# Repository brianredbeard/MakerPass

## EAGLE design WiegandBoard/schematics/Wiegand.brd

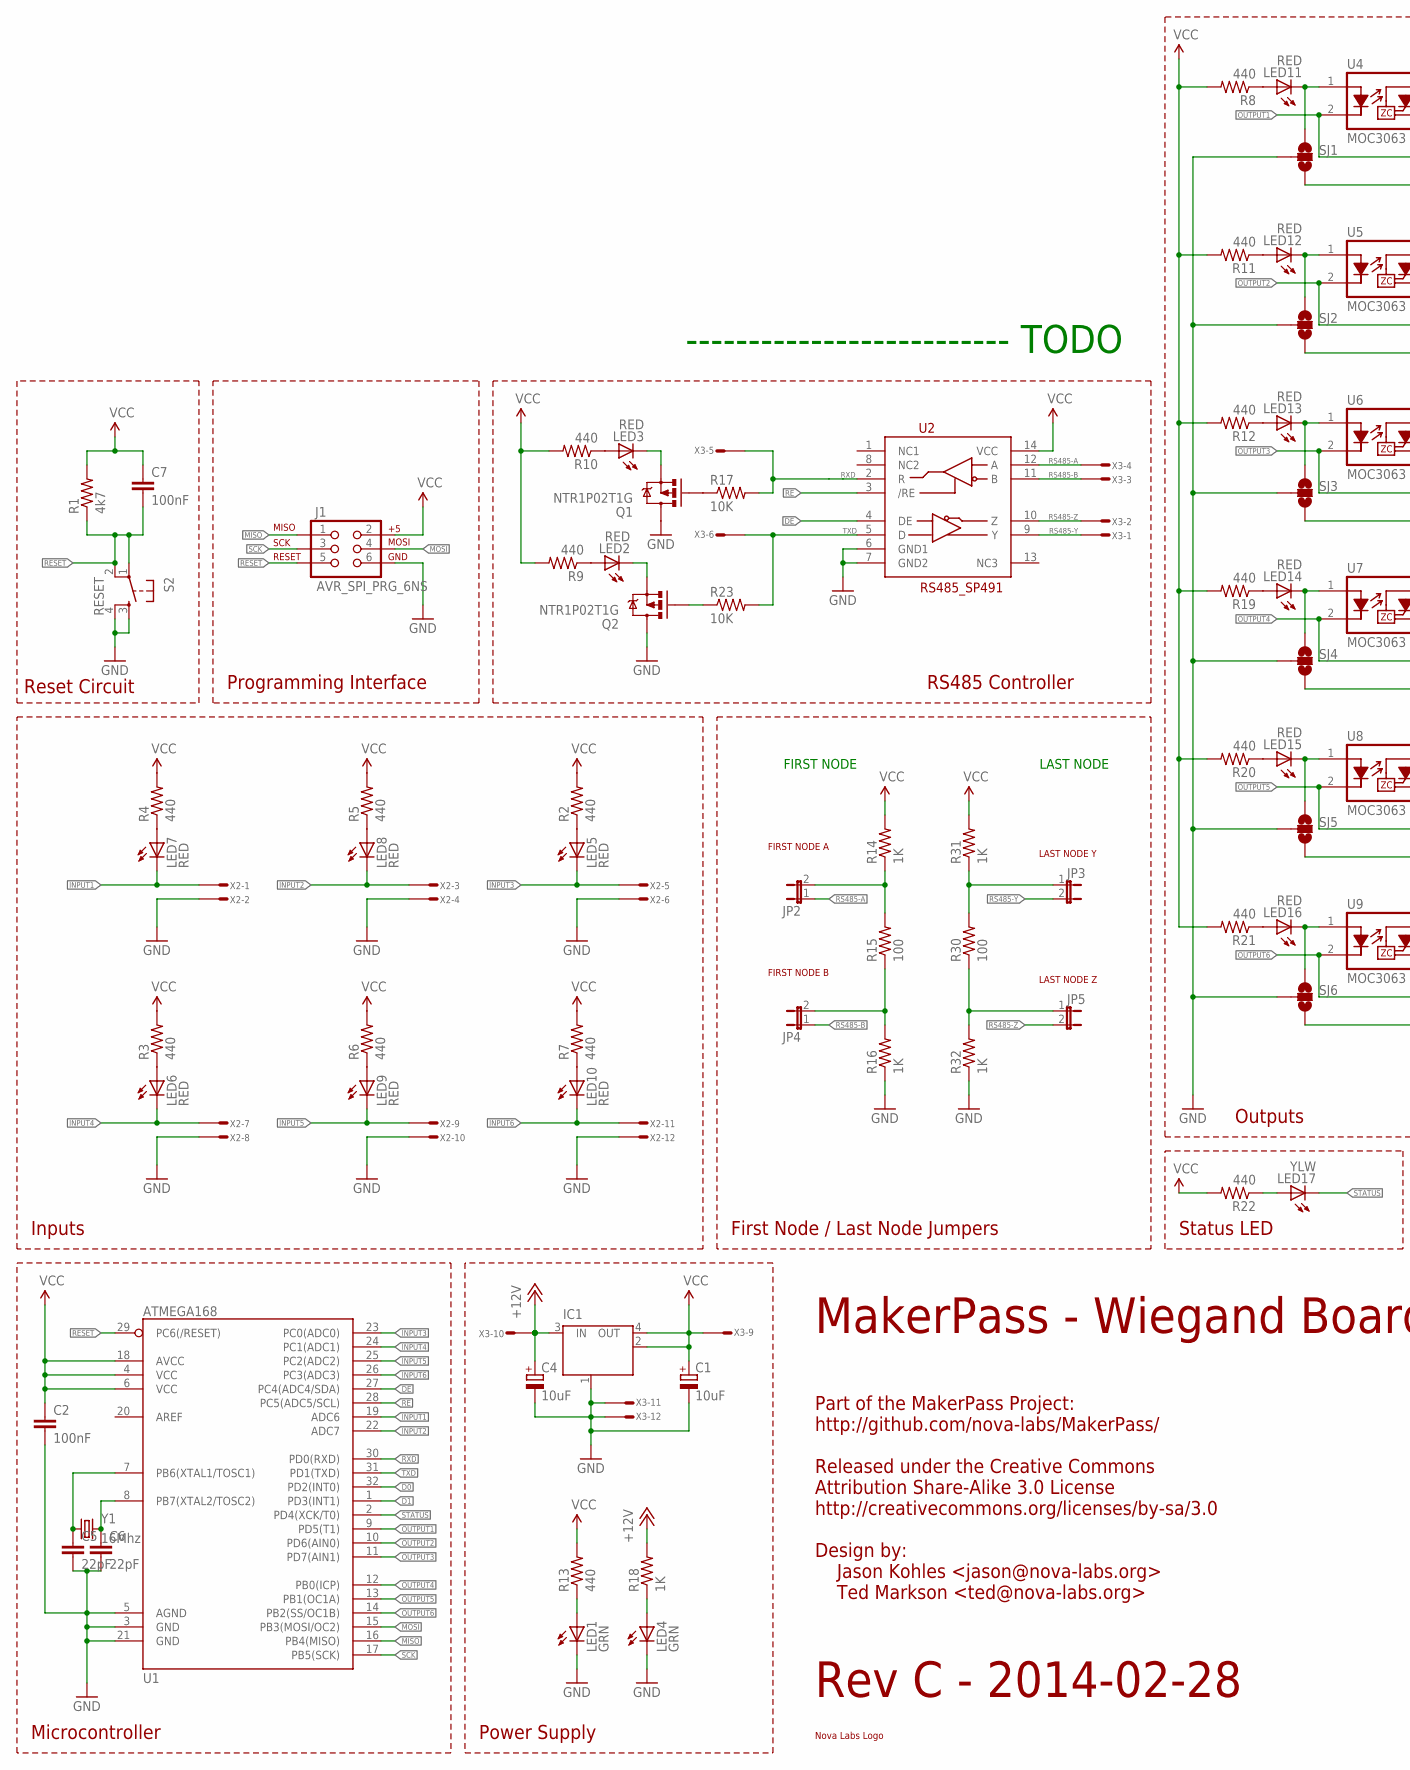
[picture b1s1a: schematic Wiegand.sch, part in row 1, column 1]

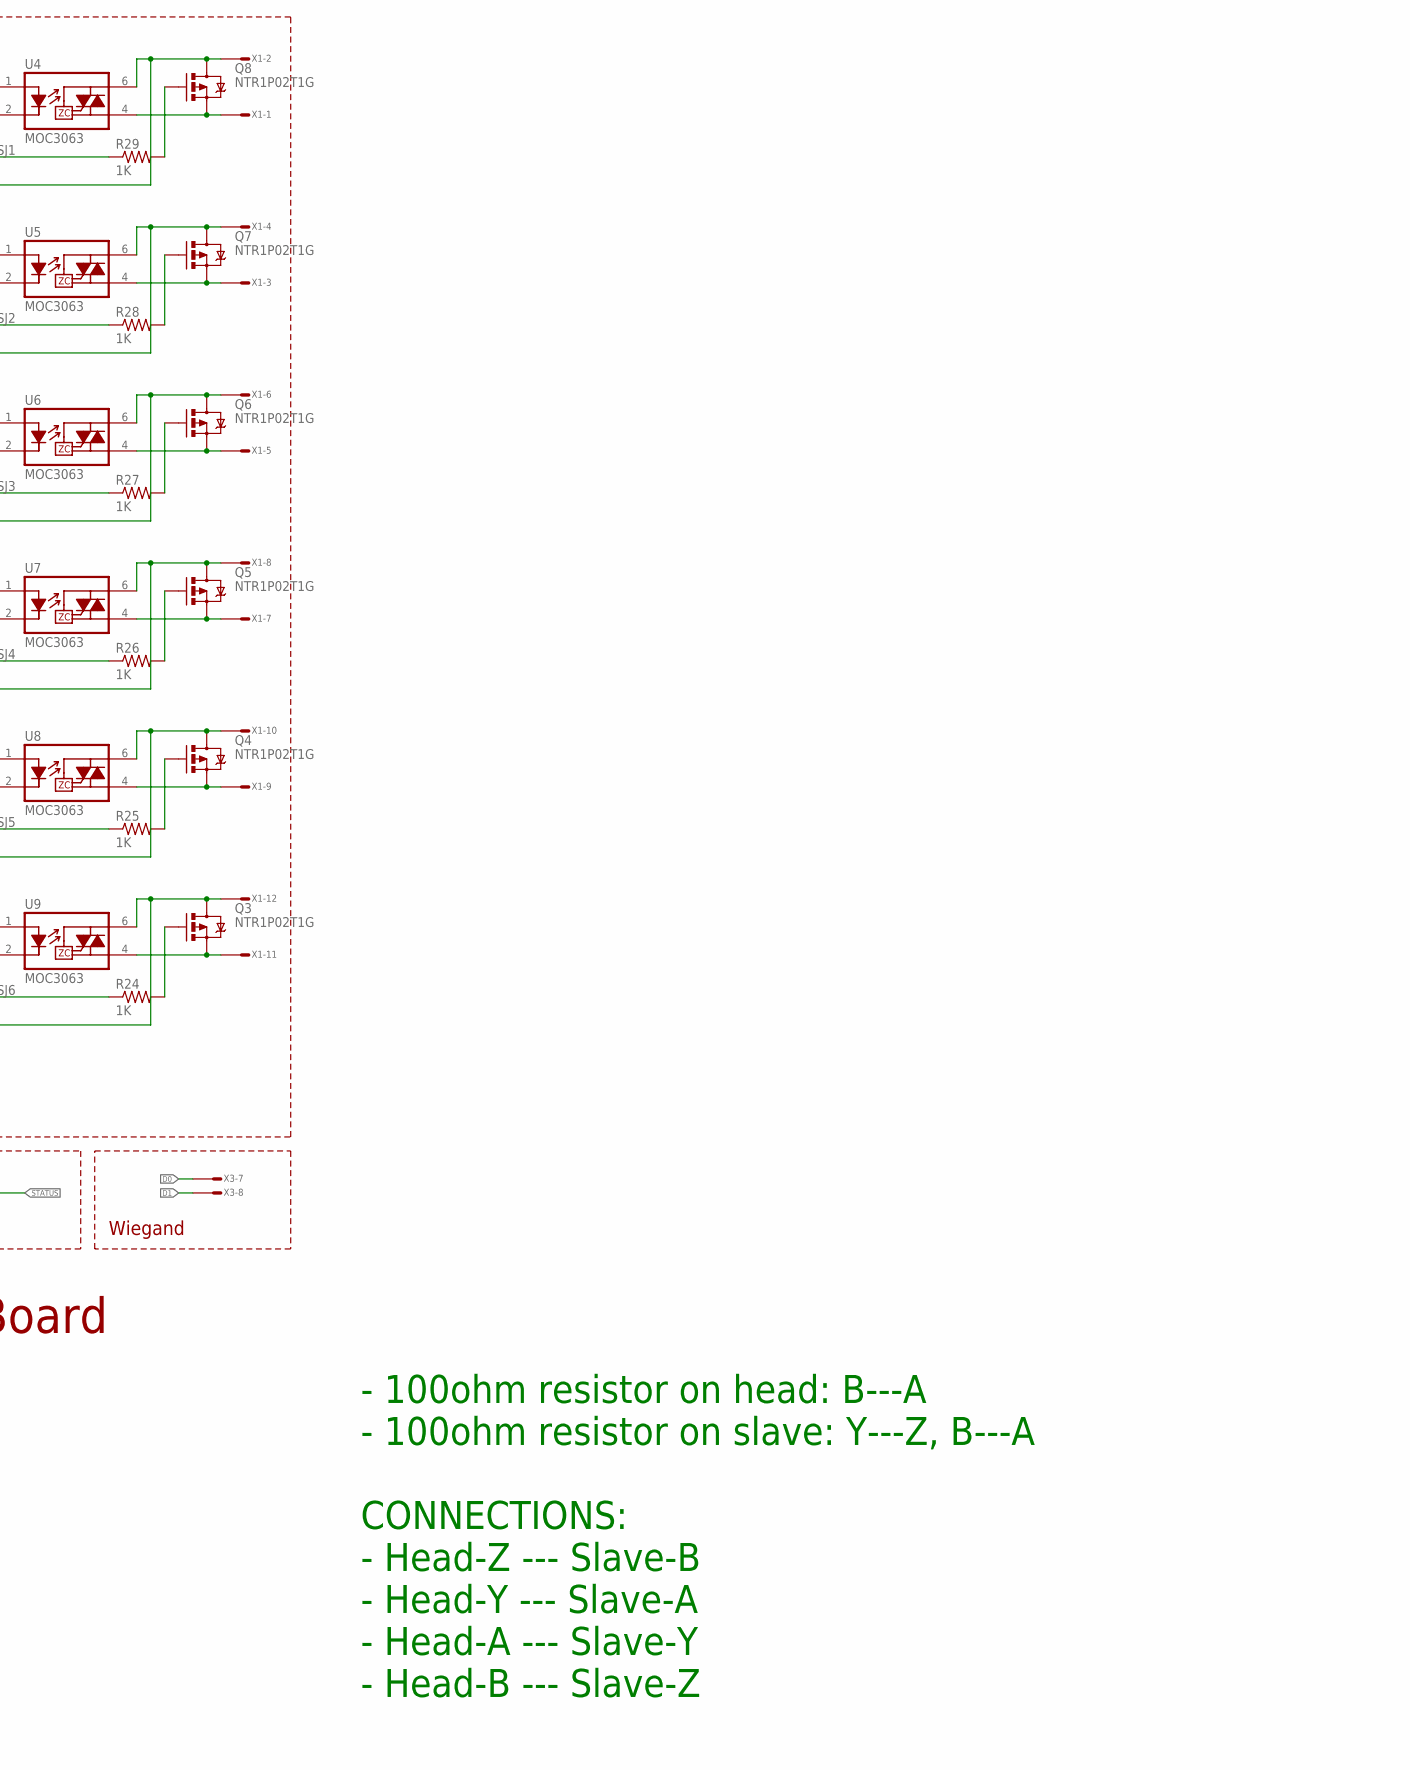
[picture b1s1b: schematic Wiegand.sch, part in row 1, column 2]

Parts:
C1, C4: 10uF; PANASONIC_D; MFG_PN EMVA250ADA100MD55G
C2, C7: 100nF; 0603-CAP; MFG_PN 0603YC104KAT2A
C5, C6: 22pF; 0603-CAP; MFG_PN 06035A220JAT2A
IC1: MC33269ST-3.3T3; SOT223; MFG_PN NCP1117ST50T3G
J1: AVR_SPI_PRG_6NS; 2X3-NS
JP2, JP3, JP4, JP5: JUMPER-2PTH; 1X02; MFG_PN 1x2 pin header
LED1, LED4: GRN; LED-805; MFG_PN LG R971-KN-1
LED2, LED3, LED5, LED6, LED7, LED8, LED9, LED10, LED11, LED12, LED13, LED14, LED15, LED16: RED; LED-805; MFG_PN LH R974-LP-1
LED17: YLW; LED-805; MFG_PN LY R976-PS-36
Q1, Q2, Q3, Q4, Q5, Q6, Q7, Q8: NTR1P02T1G; SOT23-3; MFG_PN NTR1P02T1G
R1: 4k7; 0603-RES; MFG_PN ERJ-3GEYJ472V
R2, R3, R4, R5, R6, R7, R8, R9, R10, R11, R12, R13, R19, R20, R21, R22: 440; 0603-RES; MFG_PN ERJ3EKF3300V
R14, R16, R18, R24, R25, R26, R27, R28, R29, R31, R32: 1K; 0603-RES; MFG_PN ERJ-3EKF1001V
R15, R30: 100; 0603-RES; MFG_PN ERJ-3EKF1001V
R17, R23: 10K; 0603-RES; MFG_PN ERJ3EKF3300V
S2: RESET; TACTILE_SWITCH_SMD; MFG_PN PTS525SM10SMTRLFS
SJ1, SJ2, SJ3, SJ4, SJ5, SJ6: SOLDERJUMPER_2WAY-TRACE1&2&3; SJ_3_WIRE1&2&3
U1: ATMEGA168; TQFP32-08; MFG_PN ATMEGA168-20AU
U2: RS485_SP491; SOIC-14; MFG_PN SP491EEN-L
U4, U5, U6, U7, U8, U9: MOC3063; DIP8SMD; MFG_PN MOC3063S-TA1
X1, X2, X3: CON-1X12-TERMBLOCK-3.5MM; MFG_PN OSTTE120104
X4: NOVA-LABS-LOGO-SILK-400MIL
Y1: 16Mhz; HC49UP; MFG_PN FOXSDLF/160-20

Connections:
+12V: C4.+, IC1.3 (IN), R18.2, X3.10
D0: U1.32 (PD2(INT0)), X3.7
D1: U1.1 (PD3(INT1)), X3.8
DE: U1.27 (PC4(ADC4/SDA)), U2.4 (DE)
GND: C1.-, C2.2, C4.-, C5.2, C6.2, IC1.1 (GND/ADJ), J1.6, LED1.C, LED4.C, Q1.3 (D), Q2.3 (D), R16.1, R32.1, S2.3, S2.4, SJ1.2, SJ2.2, SJ3.2, SJ4.2, SJ5.2, SJ6.2, U1.3 (GND), U1.5 (AGND), U1.21 (GND), U2.6 (GND1), U2.7 (GND2), X2.2, X2.4, X2.6, X2.8, X2.10, X2.12, X3.11, X3.12
INPUT1: LED7.C, U1.19 (ADC6), X2.1
INPUT2: LED8.C, U1.22 (ADC7), X2.3
INPUT3: LED5.C, U1.23 (PC0(ADC0)), X2.5
INPUT4: LED6.C, U1.24 (PC1(ADC1)), X2.7
INPUT5: LED9.C, U1.25 (PC2(ADC2)), X2.9
INPUT6: LED10.C, U1.26 (PC3(ADC3)), X2.11
MISO: J1.1, U1.16 (PB4(MISO))
MOSI: J1.4, U1.15 (PB3(MOSI/OC2))
unnamed: LED1.A, R13.1
unnamed: Q4.2 (S), U8.4 (T2), X1.9
unnamed: Q4.3 (D), SJ5.3, U8.6 (T1), X1.10
unnamed: LED5.A, R2.1
unnamed: JP5.1, R30.1, R32.2
unnamed: JP3.1, R30.2, R31.1
unnamed: LED4.A, R18.1
unnamed: LED3.C, Q1.2 (S)
unnamed: LED6.A, R3.1
unnamed: LED7.A, R4.1
unnamed: LED8.A, R5.1
unnamed: LED9.A, R6.1
unnamed: LED10.A, R7.1
unnamed: LED11.C, SJ1.1, U4.1 (A)
unnamed: LED11.A, R8.1
unnamed: Q8.3 (D), SJ1.3, U4.6 (T1), X1.2
unnamed: Q7.2 (S), U5.4 (T2), X1.3
unnamed: Q7.3 (D), SJ2.3, U5.6 (T1), X1.4
unnamed: LED12.A, R11.1
unnamed: LED12.C, SJ2.1, U5.1 (A)
unnamed: Q6.2 (S), U6.4 (T2), X1.5
unnamed: Q6.3 (D), SJ3.3, U6.6 (T1), X1.6
unnamed: LED13.A, R12.1
unnamed: LED2.A, R9.1
unnamed: LED3.A, R10.1
unnamed: LED13.C, SJ3.1, U6.1 (A)
unnamed: Q5.2 (S), U7.4 (T2), X1.7
unnamed: Q5.3 (D), SJ4.3, U7.6 (T1), X1.8
unnamed: LED14.A, R19.1
unnamed: LED14.C, SJ4.1, U7.1 (A)
unnamed: LED2.C, Q2.2 (S)
unnamed: Q1.1 (G), R17.1
unnamed: LED15.A, R20.1
unnamed: LED15.C, SJ5.1, U8.1 (A)
unnamed: Q3.3 (D), SJ6.3, U9.6 (T1), X1.12
unnamed: Q3.2 (S), U9.4 (T2), X1.11
unnamed: LED16.A, R21.1
unnamed: LED16.C, SJ6.1, U9.1 (A)
unnamed: LED17.A, R22.1
unnamed: Q2.1 (G), R23.1
unnamed: Q4.1 (G), R25.2
unnamed: Q5.1 (G), R26.2
unnamed: Q6.1 (G), R27.2
unnamed: Q7.1 (G), R28.2
unnamed: Q8.1 (G), R29.2
unnamed: JP2.2, R14.1, R15.2
unnamed: JP4.2, R15.1, R16.2
unnamed: Q8.2 (S), U4.4 (T2), X1.1
unnamed: C5.1, U1.7 (PB6(XTAL1/TOSC1)), Y1.1
unnamed: C6.1, U1.8 (PB7(XTAL2/TOSC2)), Y1.2
unnamed: Q3.1 (G), R24.2
OUTPUT1: R29.1, U1.9 (PD5(T1)), U4.2 (K)
OUTPUT2: R28.1, U1.10 (PD6(AIN0)), U5.2 (K)
OUTPUT3: R27.1, U1.11 (PD7(AIN1)), U6.2 (K)
OUTPUT4: R26.1, U1.12 (PB0(ICP)), U7.2 (K)
OUTPUT5: R25.1, U1.13 (PB1(OC1A)), U8.2 (K)
OUTPUT6: R24.1, U1.14 (PB2(SS/OC1B)), U9.2 (K)
RE: U1.28 (PC5(ADC5/SCL)), U2.3 (/RE)
RESET: C7.2, J1.5, R1.1, S2.1, S2.2, U1.29 (PC6(/RESET))
RS485-A: JP2.1, U2.12 (A), X3.4
RS485-B: JP4.1, U2.11 (B), X3.3
RS485-Y: JP3.2, U2.9 (Y), X3.1
RS485-Z: JP5.2, U2.10 (Z), X3.2
RXD: R17.2, U1.30 (PD0(RXD)), U2.2 (R), X3.5
SCK: J1.3, U1.17 (PB5(SCK))
STATUS: LED17.C, U1.2 (PD4(XCK/T0))
TXD: R23.2, U1.31 (PD1(TXD)), U2.5 (D), X3.6
VCC: C1.+, C2.1, C7.1, IC1.2 (OUT), IC1.4 (OUT), J1.2, R1.2, R2.2, R3.2, R4.2, R5.2, R6.2, R7.2, R8.2, R9.2, R10.2, R11.2, R12.2, R13.2, R14.2, R19.2, R20.2, R21.2, R22.2, R31.2, U1.4 (VCC), U1.6 (VCC), U1.18 (AVCC), U2.14 (VCC), X3.9

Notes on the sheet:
RS485 Controller
Programming Interface
Power Supply
Reset Circuit
Wiegand
Part of the MakerPass Project: http://github.com/nova-labs/MakerPass/ Released under the Creative Commons Attribution Share-Alike 3.0 License http://creativecommons.org/licenses/by-sa/3.0 Design by: Jason Kohles <jason@nova-labs.org> Ted Markson <ted@nova-labs.org>
Status LED
First Node / Last Node Jumpers
Outputs
Inputs
Microcontroller
MakerPass - Wiegand Board
Rev C - 2014-02-28
FIRST NODE
LAST NODE
-------------------------- TODO
- 100ohm resistor on head: B---A - 100ohm resistor on slave: Y---Z, B---A CONNECTIONS: - Head-Z --- Slave-B - Head-Y --- Slave-A - Head-A --- Slave-Y - Head-B --- Slave-Z
FIRST NODE A
FIRST NODE B
LAST NODE Z
LAST NODE Y

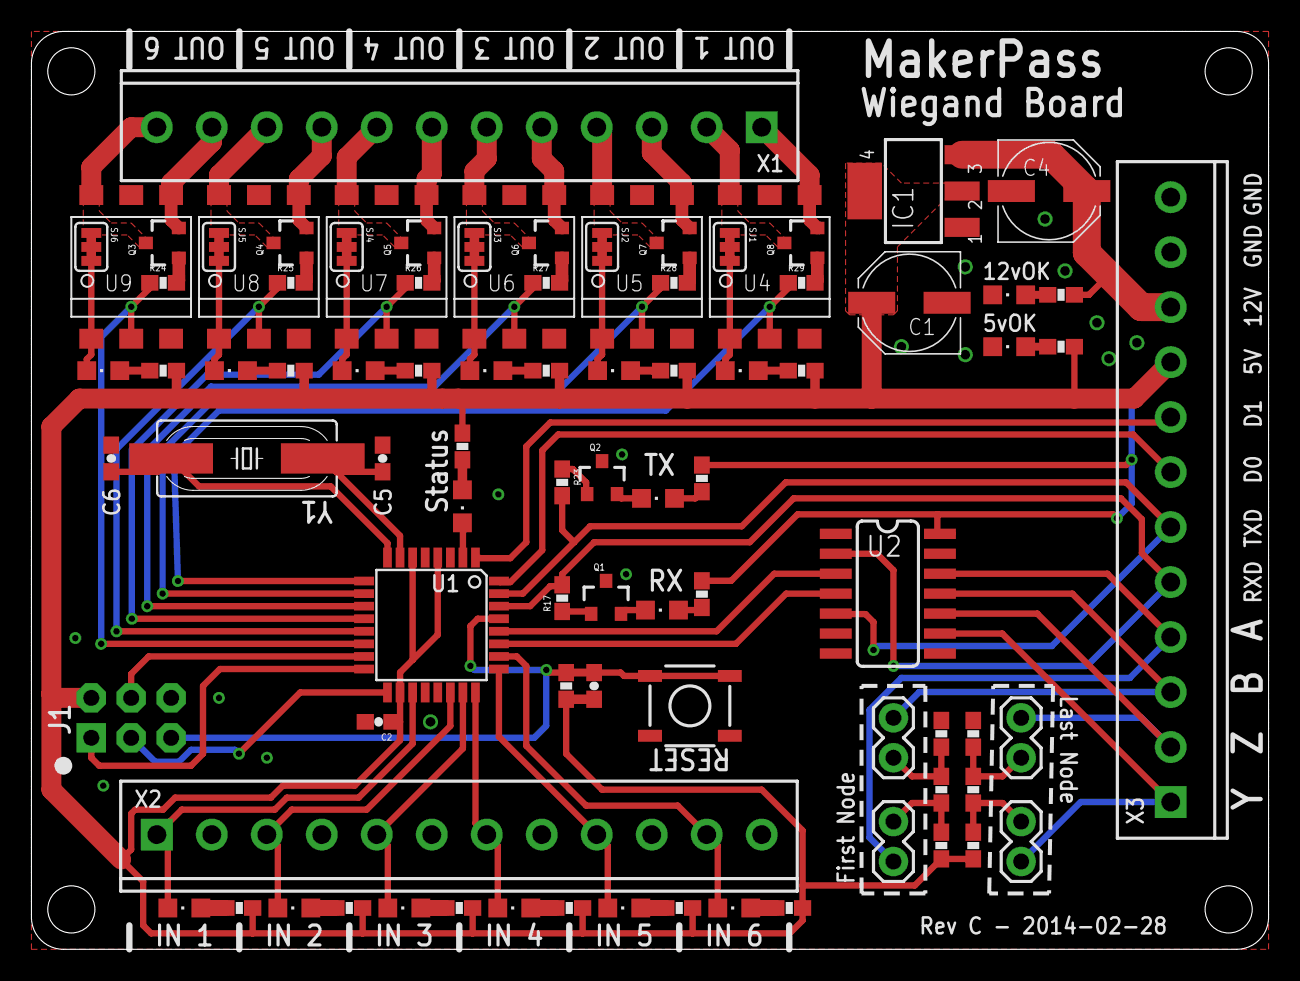
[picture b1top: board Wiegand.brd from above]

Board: 2 copper layers, 78.7 x 58.4 mm, 89 parts (1 on the bottom side), 81 nets.

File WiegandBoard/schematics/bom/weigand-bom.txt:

Partlist exported from C:/Users/tcm/Owncloud/nova-labs/MakerPass/WiegandBoard/schematics/Wiegand.sch at 2/24/2014 2:30:15 AM

Qty Value           Device                   Package                  Parts                                                                                     Description                                            MFG_PN            
3                   CON-1X12-TERMBLOCK-3.5MM CON-1X12-TERMBLOCK-3.5MM X1, X2, X3                                                                                CON-1X12                                               OSTTE120104       
1                   MC33269ST-3.3T3          SOT223                   IC1                                                                                       Adjustable Output Low Dropout Voltage Regulator 800 mA NCP1117ST50T3G    
6                   NPN-BEC-SOT23-3          SOT23-3                  Q3, Q4, Q5, Q6, Q7, Q8                                                                    Transistor NPN                                                           
6                   SOLDERJUMPER_2WAYS       SJ_3                     SJ1, SJ2, SJ3, SJ4, SJ5, SJ6                                                              Solder Jumper                                                            
2   100             RESISTOR0603-RES         0603-RES                 R15, R30                                                                                  Resistor                                               ERJ-3EKF1001V     
2   100nF           CAP0603-CAP              0603-CAP                 C2, C7                                                                                    Capacitor                                              0603YC104KAT2A    
2   10K             RESISTOR0603-RES         0603-RES                 R17, R23                                                                                  Resistor                                               ERJ3EKF3300V      
2   10uF            CPOL-EUD                 PANASONIC_D              C1, C4                                                                                    POLARIZED CAPACITOR, European symbol                   EMVA250ADA100MD55G
1   16Mhz           CRYSTALSMD               HC49UP                   Y1                                                                                        Crystals                                               FOXSDLF/160-20    
11  1K              RESISTOR0603-RES         0603-RES                 R14, R16, R18, R24, R25, R26, R27, R28, R29, R31, R32                                     Resistor                                               ERJ-3EKF1001V     
2   22pF            CAP0603-CAP              0603-CAP                 C5, C6                                                                                    Capacitor                                              06035A220JAT2A    
16  440             RESISTOR0603-RES         0603-RES                 R2, R3, R4, R5, R6, R7, R8, R9, R10, R11, R12, R13, R19, R20, R21, R22                    Resistor                                               ERJ3EKF3300V      
1   4k7             RESISTOR0603-RES         0603-RES                 R1                                                                                        Resistor                                               ERJ-3GEYJ472V     
1   ATMEGA168       ATMEGA168                TQFP32-08                U1                                                                                        Atmel 32-pin 8-bit micro, 16k flash.                   ATMEGA168-20AU    
1   AVR_SPI_PRG_6NS AVR_SPI_PRG_6NS          2X3-NS                   J1                                                                                        AVR ISP 6 Pin                                                            
1   First Node A    JUMPER-2PTH              1X02                     JP2                                                                                       Jumper                                                 1x2 pin header    
1   First Node B    JUMPER-2PTH              1X02                     JP4                                                                                       Jumper                                                 1x2 pin header    
2   GRN             LED-0805                 LED-805                  LED1, LED4                                                                                Light Emitting Diode                                   LG R971-KN-1      
1   Last Node Y     JUMPER-2PTH              1X02                     JP3                                                                                       Jumper                                                 1x2 pin header    
1   Last Node Z     JUMPER-2PTH              1X02                     JP5                                                                                       Jumper                                                 1x2 pin header    
6   MOC3063         MOC3063S                 DIP8SMD                  U4, U5, U6, U7, U8, U9                                                                    Optotriac in DIP and SMD                               MOC3063M          
2   NTR1P02T1G      MOSFET-PCHANNELSMD       SOT23-3                  Q1, Q2                                                                                                                                           NTR1P02T1G        
14  RED             LED-0805                 LED-805                  LED2, LED3, LED5, LED6, LED7, LED8, LED9, LED10, LED11, LED12, LED13, LED14, LED15, LED16 Light Emitting Diode                                   LY R976-PS-36     
1   RESET           TAC_SWITCHSMD            TACTILE_SWITCH_SMD       S2                                                                                        Momentary Switch                                       PTS525SM10SMTRLFS 
1   RS485_SP491     RS485_SP491              SOIC-14                  U2                                                                                                                                               SP491EEN-L        
1   YLW             LED-0805                 LED-805                  LED17                                                                                     Light Emitting Diode                                   LY R976-PS-36

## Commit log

2014-02-13 minor changes to board, adding firmware and eagleup render
2014-02-13 change tasks to readme so it shows on github page
2014-02-13 added dimensions and changed rev number in brd file, new eagleup render
2014-02-13 fix format
2014-02-20 added separate resistors for first / last node, added transistor option atop optoisolators
2014-02-22 minor edits to brd, rerendered eagleup model
2014-02-22 moved features list to wiki
2014-02-23 minor edits to brd
2014-02-28 put files in wiegandboard project folder
2014-03-25 update example authenticator
2014-04-03 REVC boards made
2015-03-05 Initial makerpass nodeconfig

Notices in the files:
parts and their libraries:
SparkFun: Licensing: CC v3.0 Share-Alike You are welcome to use this library for commercial purposes.
